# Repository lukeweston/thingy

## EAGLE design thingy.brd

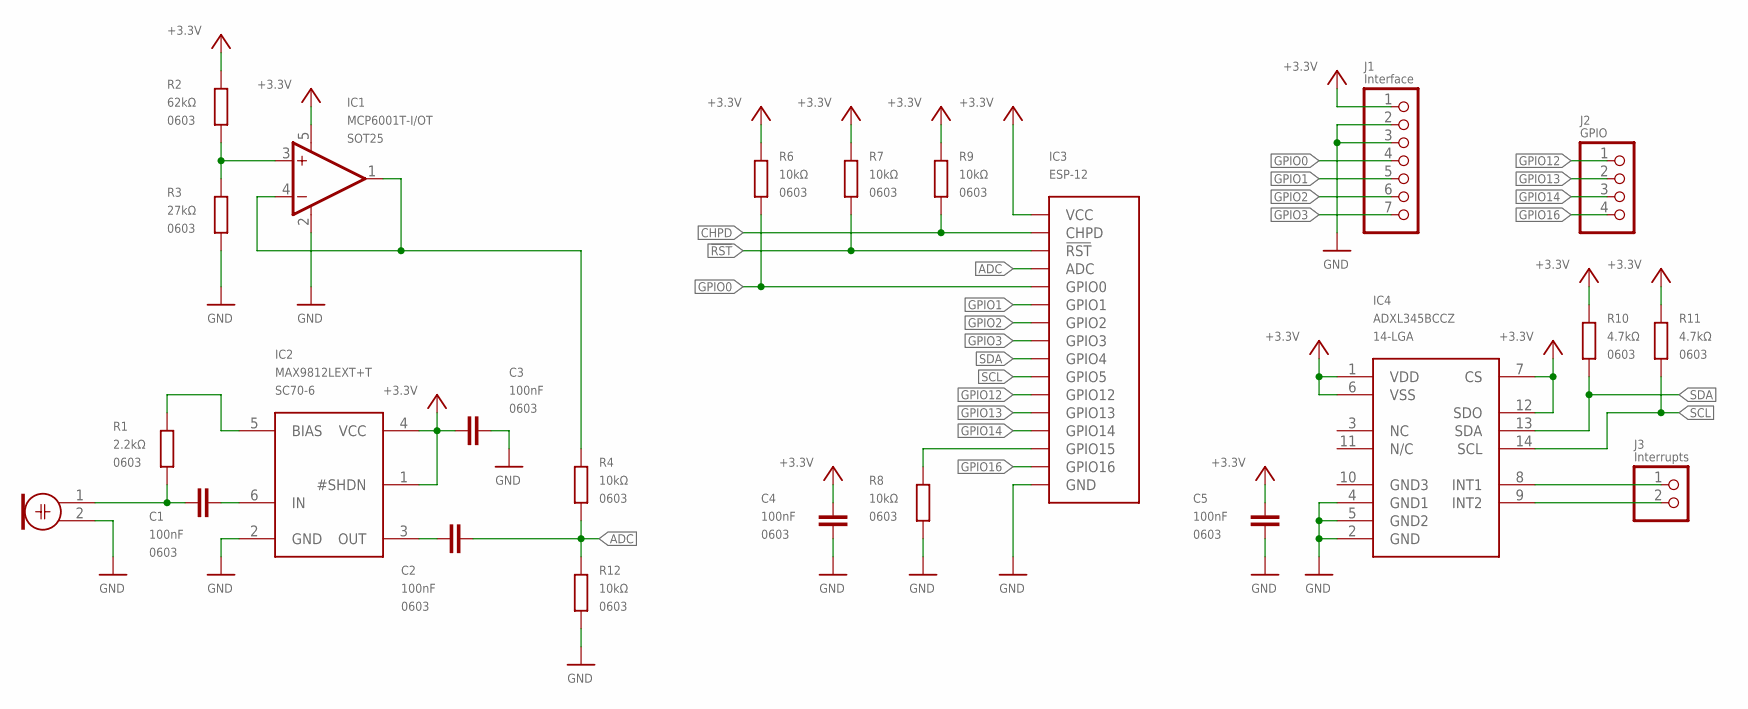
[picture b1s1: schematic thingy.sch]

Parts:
C1, C2, C3, C4, C5: 100nF; 0603
IC1: MCP6001T-I/OT; SOT23-5
IC2: MAX9812LEXT+T; SC-70-6
IC3: ESP-12
IC4: ADXL345BCCZ; LGA14
J1: Interface; 1X07
J2: GPIO; 1X04
J3: Interrupts; 1X02
Q1: Electret Mic; WM-64PN
R1: 2.2kΩ; 0603
R2: 62kΩ; 0603
R3: 27kΩ; 0603
R4, R6, R7, R8, R9, R12: 10kΩ; 0603
R10, R11: 4.7kΩ; 0603

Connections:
!RST: IC3.RST (!RST), R7.1
+3.3V: C3.1, C4.1, C5.1, IC1.5 (V+), IC2.1 (#SHDN), IC2.4 (VCC), IC3.VCC, IC4.1 (VDD), IC4.6 (VSS), IC4.7 (CS), IC4.12 (SDO), J1.1, R2.2, R6.2, R7.2, R9.2, R10.2, R11.2
ACC_INT1: IC4.8 (INT1), J3.1
ACC_INT2: IC4.9 (INT2), J3.2
ADC: C2.2, IC3.ADC, R4.1, R12.2
CHPD: IC3.CHPD, R9.1
GND: C3.2, C4.2, C5.2, IC1.2 (V-), IC2.2 (GND), IC3.GND, IC4.2 (GND), IC4.4 (GND1), IC4.5 (GND2), J1.2, J1.3, Q1.2, R3.1, R8.1, R12.1
GPIO0: IC3.GPIO0, J1.4, R6.1
GPIO1: IC3.GPIO1, J1.5
GPIO2: IC3.GPIO2, J1.6
GPIO3: IC3.GPIO3, J1.7
GPIO12: IC3.GPIO12, J2.1
GPIO13: IC3.GPIO13, J2.2
GPIO14: IC3.GPIO14, J2.3
GPIO16: IC3.GPIO16, J2.4
unnamed: IC1.1 (OUT), IC1.4 (-IN), R4.2
unnamed: IC3.GPIO15, R8.2
unnamed: IC1.3 (+IN), R2.1, R3.2
unnamed: C2.1, IC2.3 (OUT)
unnamed: C1.1, Q1.1, R1.1
unnamed: C1.2, IC2.6 (IN)
unnamed: IC2.5 (BIAS), R1.2
SCL: IC3.GPIO5, IC4.14 (SCL), R11.1
SDA: IC3.GPIO4, IC4.13 (SDA), R10.1

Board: 2 copper layers, 24 parts (0 on the bottom side), 24 nets, no tracks yet.

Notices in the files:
parts and their libraries:
MAX9812: License : GNU General Public License version 2 (see bottom)
